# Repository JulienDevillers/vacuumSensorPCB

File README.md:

# vacuumSensorPCB
PCB for vacuum sensor for DIY pick and place machines

It is based on this design: https://makr.zone/vacuum-sensor/192/

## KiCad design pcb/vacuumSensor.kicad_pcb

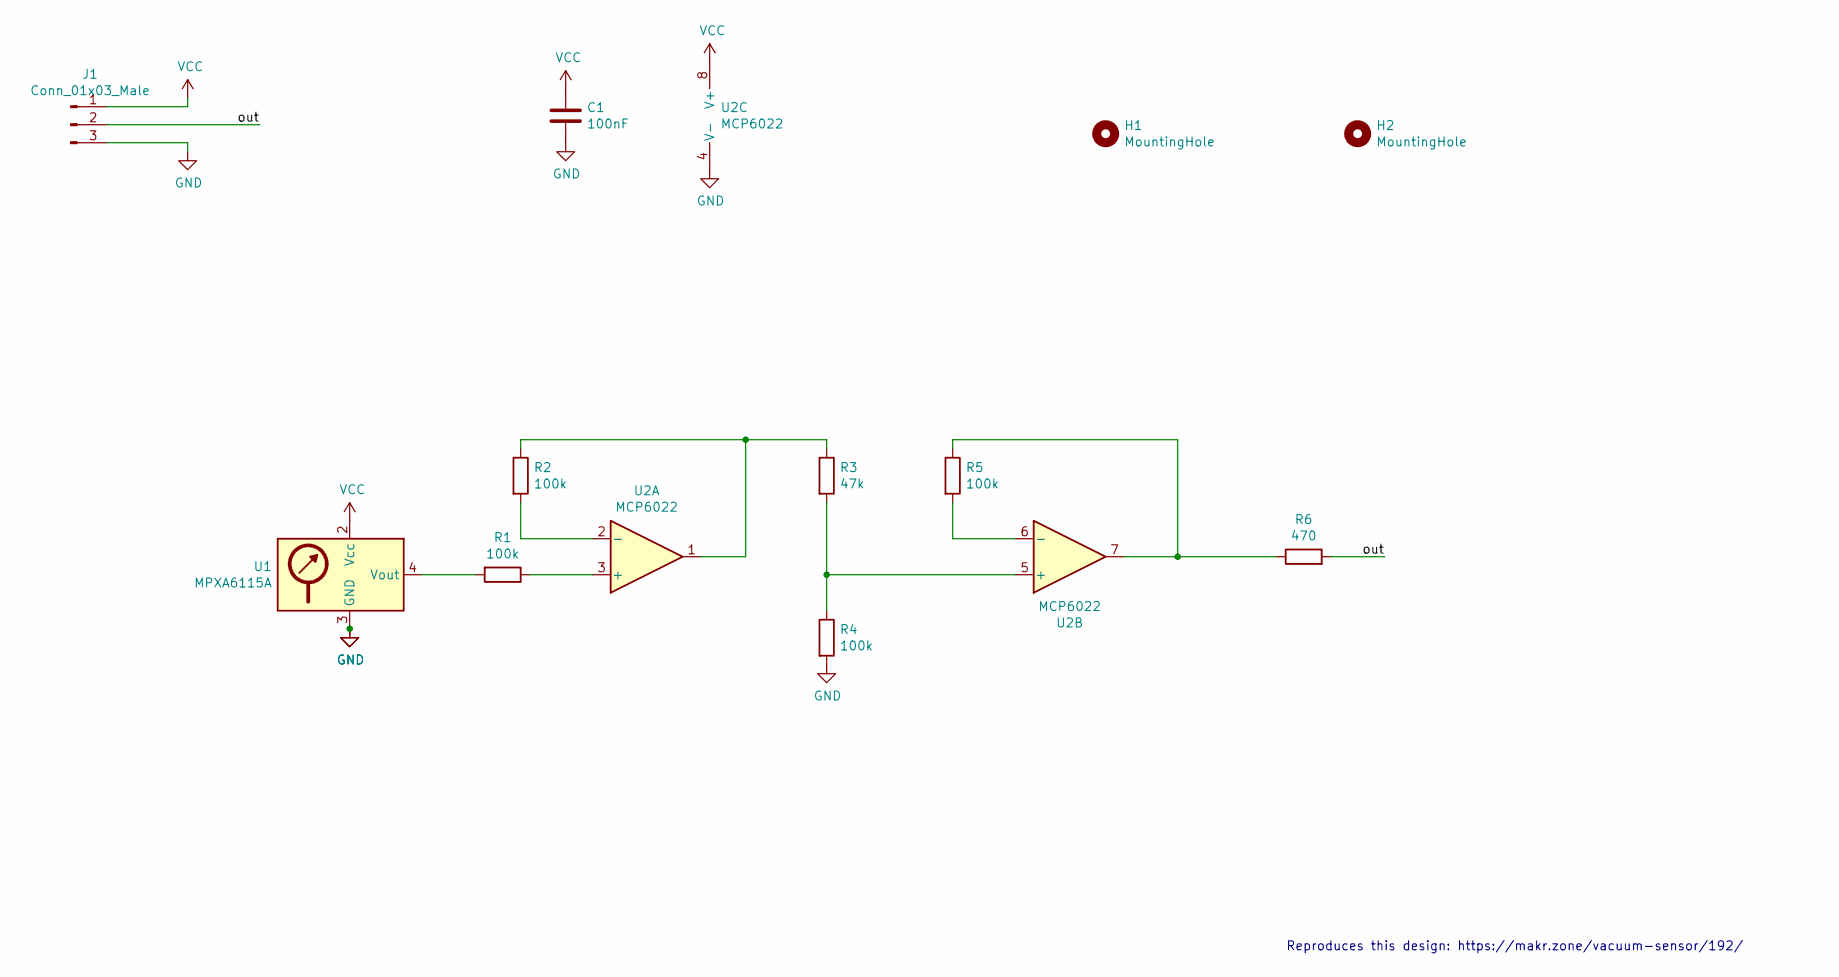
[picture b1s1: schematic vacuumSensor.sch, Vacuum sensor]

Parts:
C1: 100nF; C_0603_1608Metric
H1, H2: MountingHole; MountingHole_3.2mm_M3
J1: Conn_01x03_Male; PinHeader_1x03_P2.54mm_Vertical
R1, R2, R4, R5: 100k; R_0603_1608Metric
R3: 47k; R_0603_1608Metric
R6: 470; R_0603_1608Metric
U1: MPXA6115A; SOP8-15mm
U2: MCP6022; SOIC-8_3.9x4.9mm_P1.27mm

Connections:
/out: J1.2, R6.2
GND: C1.2, J1.3, R4.2, U1.3 (GND), U2.4 (V-)
unnamed: R1.1, U2.3 (+)
unnamed: R1.2, U1.4 (Vout)
unnamed: R2.1, R3.1, U2.1
unnamed: R2.2, U2.2 (-)
unnamed: R3.2, R4.1, U2.5 (+)
unnamed: R5.1, R6.1, U2.7
unnamed: R5.2, U2.6 (-)
VCC: C1.1, J1.1, U1.2 (Vcc), U2.8 (V+)

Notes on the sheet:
Reproduces this design: https://makr.zone/vacuum-sensor/192/

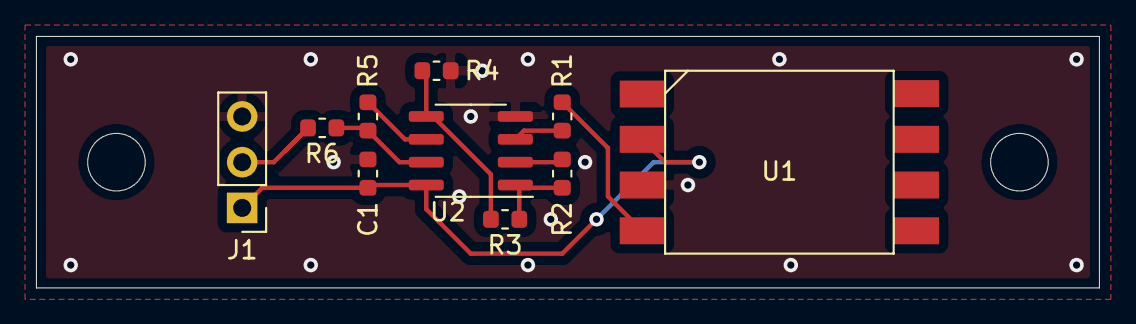
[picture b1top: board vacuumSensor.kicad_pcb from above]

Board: 2 copper layers, 59.1 x 14.0 mm, 12 parts (0 on the bottom side), 10 nets.

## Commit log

2020-10-06 Creation
2020-10-06 visual changes
2020-10-06 Added text info to schematic.
2020-10-06 Added pictures
2020-10-06 Added images.
2020-10-06 Smaller image.
